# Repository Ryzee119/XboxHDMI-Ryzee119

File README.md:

# Original Xbox 100% Digital HDMI (Prototype)

**Note: This is a 'working' but unfinished prototype. I don't plan to improve this further. See https://makemhz.com/products/xboxhd for a properly finished product with way more features.**

* A few HDMI captures taken from this board are here: https://imgur.com/a/OkmB1Vs
* This is a prototype 100% digital Original Xbox HDMI addon PCB. It taps into the GPU pixel bus before it enters the analog video encoder and converts it to a HDMI compliant signal.
* It has not been fully tested and may not work for you. Use at your own risk. This should only really be a starting point to make something better.
* SPDIF digital audio is tapped off the Xbox motherboard and is also encoded into the HDMI signal for the best possible audio quality.
* This is a prototype board which should work on all Xbox revisions however a new flex would need to be designed to accomodate v1.6 motherboards with an Xcalibur encoder.
* 480i does not work reliably. Use a force 480p BIOS.
* The xbox kernels video modes are not compliant to proper HDMI signalling (v/hsync, porch delays etc). This does not have the ability to correct that. If your display is picky it may just not display anything.
* Currently the MakeMHz solution is recommended. https://makemhz.com/products/xboxhd. It is a completely independent design which has been much more tested and with more features.

## Bill of materials
* See [Kitspace](https://kitspace.org/boards/github.com/ryzee119/XboxHDMI-Ryzee119/).
* Flatflex must be ordered separately. See [hardware](./hardware).

## Design Files
* Source code for the STM32F0 driver is [here](./src).
* Hardware design files are [here](./hardware).

## Programming
* Compile the code with [VSCode](https://code.visualstudio.com/) and the [platformIO](https://platformio.org/install/ide?install=vscode) plugin. It should automatically create the build sytem. Just click build.
* The STM32F07 driver must be programmed with the firmware.
* Programming is through the 5 pin SWD header on the PCB. Pinout from left to right: `+3V3, SWDCLK, GND, SWDIO, NRST`
* Some debug output is via the pad labelled `TX`. Baud 115200.

## Installation

* Photo may not match final PCB layout.

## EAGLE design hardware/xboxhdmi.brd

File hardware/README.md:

# Hardware

* This board was designed using [Autodesk Eagle](https://www.autodesk.com/products/eagle/overview). You can edit the `.brd` and `.sch` with this program.

## View Gerbers
* [XboxHDMI PCB](https://tracespace.io/view/?boardUrl=https://github.com/Ryzee119/XboxHDMI-Ryzee119/blob/master/hardware/gerbers_xboxhdmi.zip?raw=true)
* [FlatFlex PCB](https://tracespace.io/view/?boardUrl=https://github.com/Ryzee119/XboxHDMI-Ryzee119/blob/master/hardware/gerbers_conex_focus_flex.zip?raw=true)

## View Board and Schematic
* [Board](https://a360.co/3of4zFJ)
* [Schematic](https://a360.co/2LYpuQg)

## 3D Render
* [Fusion 360](https://a360.co/2KIBkxm)

### Flat Flex Properties
* 2 Layers
* Polyimide Flex
* FPC Thickness: 0.10 mm
* Stiffener: BOTTOM Plastic : 0.20 mm , BOTTOM Fr4 : 0 mm , BOTTOM Metal : 0 mm
* Total thickness at stiffener should be 0.30 mm.
* Stiffener location: See image

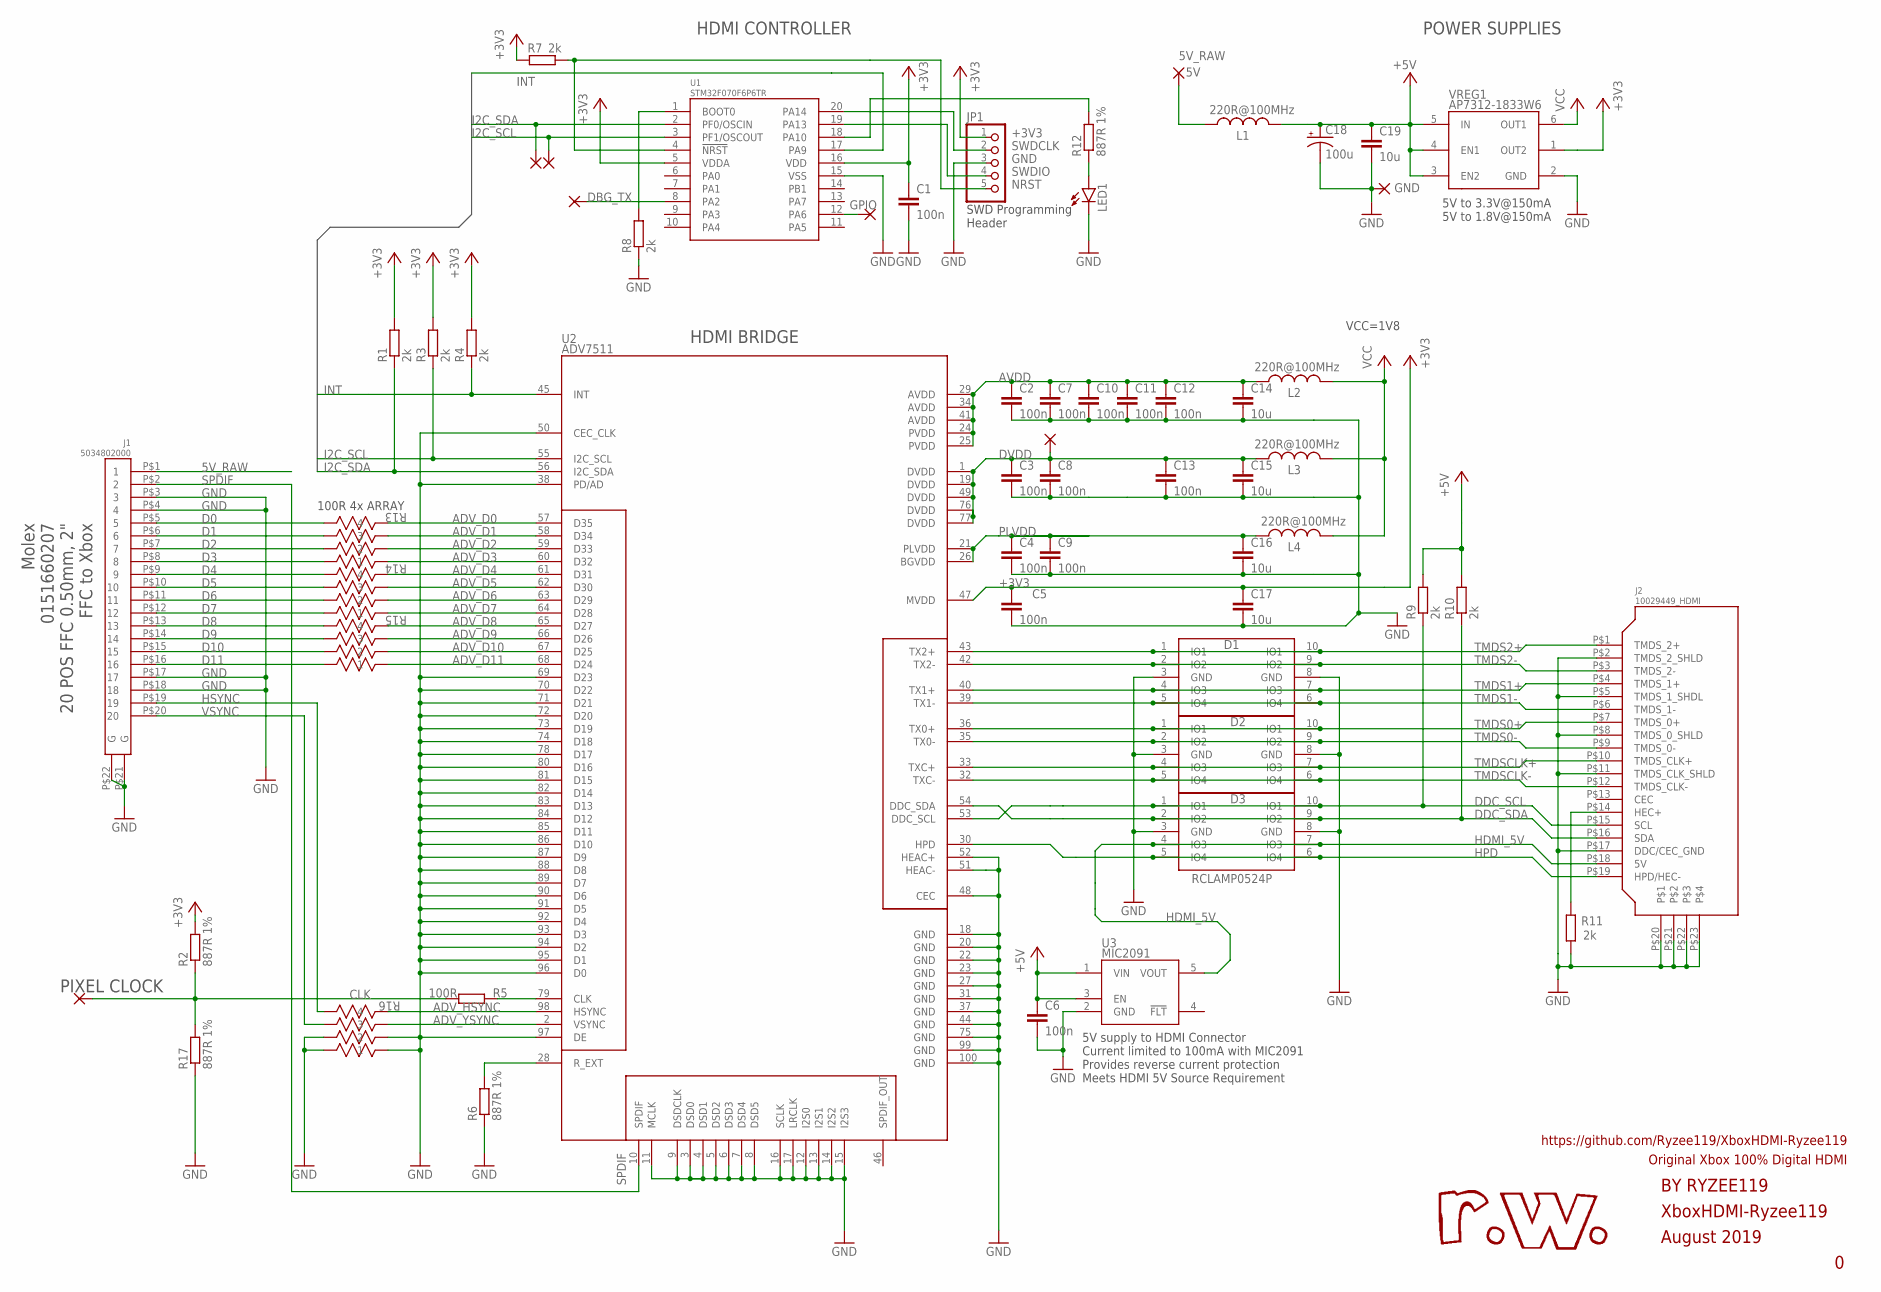
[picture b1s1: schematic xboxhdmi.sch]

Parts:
1V8, 5V: SMD2; SMD1,27-2,54
C1, C2, C3, C4, C5, C6, C7, C8, C9, C10, C11, C12, C13: 100n; C0603
C14, C15, C16, C17, C19: 10u; C1206
C18: 100u; 153CLV-0505
CLK: SMD2; SMD1,27-2,54
D1, D2, D3: RCLAMP0524P; DIOCAF50P250X100X65-10
GND: SMD2; SMD1,27-2,54
J1: 5034802000
J2: 10029449_HDMI; HDMI_10029449
JP1: PINHD-1X5; 1X05
L1, L2, L3, L4: 220R@100MHz; C0603
LED1: LEDCHIP-LED0603; CHIP-LED0603
PAD3, PAD4, PAD5: SMD2; SMD1,27-2,54
R1, R3, R4, R7, R8, R9, R10, R11: 2k; R0603
R2, R6, R12, R17: 887R 1%; R0603
R5: 100R; R0603
R13, R14, R15, R16: YC124-JR-0733RL; YAG_YC124
TX: SMD2; SMD1,27-2,54
U1: STM32F070F6P6TR; TSSOP20
U2: ADV7511; LQFP100
U3: MIC2091; SOT23-5
VREG1: AP7312-1833W6; SOT23-6

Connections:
5V_RAW: 5V.1, J1.P$1 (1), L1.1
+3V3: C1.1, C5.1, C17.1, JP1.1, R1.2, R2.2, R3.2, R4.2, R7.2, U1.5 (VDDA), U1.16 (VDD), U2.47 (MVDD), VREG1.1 (OUT2)
+5V: C6.1, C18.+, C19.1, L1.2, R9.2, R10.2, U3.1 (VIN), U3.3 (EN), VREG1.3 (EN2), VREG1.4 (EN1), VREG1.5 (IN)
ADV_CLK: R5.1, U2.79 (CLK)
ADV_D0: R13.4, U2.57 (D35)
ADV_D1: R13.3, U2.58 (D34)
ADV_D2: R13.2, U2.59 (D33)
ADV_D3: R13.1, U2.60 (D32)
ADV_D4: R14.4, U2.61 (D31)
ADV_D5: R14.3, U2.62 (D30)
ADV_D6: R14.2, U2.63 (D29)
ADV_D7: R14.1, U2.64 (D28)
ADV_D8: R15.4, U2.65 (D27)
ADV_D9: R15.3, U2.66 (D26)
ADV_D10: R15.2, U2.67 (D25)
ADV_D11: R15.1, U2.68 (D24)
ADV_HSYNC: R16.4, U2.98 (HSYNC)
ADV_YSYNC: R16.3, U2.2 (VSYNC)
AVDD: C2.1, C7.1, C10.1, C11.1, C12.1, C14.1, L2.1, U2.24 (PVDD), U2.25 (PVDD), U2.29 (AVDD), U2.34 (AVDD), U2.41 (AVDD)
CLK: CLK.1, R2.1, R5.2, R17.2
D0: J1.P$5 (5), R13.5
D1: J1.P$6 (6), R13.6
D2: J1.P$7 (7), R13.7
D3: J1.P$8 (8), R13.8
D4: J1.P$9 (9), R14.5
D5: J1.P$10 (10), R14.6
D6: J1.P$11 (11), R14.7
D7: J1.P$12 (12), R14.8
D8: J1.P$13 (13), R15.5
D9: J1.P$14 (14), R15.6
D10: J1.P$15 (15), R15.7
D11: J1.P$16 (16), R15.8
DBG_TX: TX.1, U1.8 (PA2)
DDC_SCL: D3.1 (IO1), D3.10 (IO1), J2.P$15 (SCL), R9.1, U2.53 (DDC_SCL)
DDC_SDA: D3.2 (IO2), D3.9 (IO2), J2.P$16 (SDA), R10.1, U2.54 (DDC_SDA)
DVDD: 1V8.1, C3.1, C8.1, C13.1, C15.1, L3.1, U2.1 (DVDD), U2.19 (DVDD), U2.49 (DVDD), U2.76 (DVDD), U2.77 (DVDD)
GND: C1.2, C2.2, C3.2, C4.2, C5.2, C6.2, C7.2, C8.2, C9.2, C10.2, C11.2, C12.2, C13.2, C14.2, C15.2, C16.2, C17.2, C18.-, C19.2, D1.3 (GND), D1.8 (GND), D2.3 (GND), D2.8 (GND), D3.3 (GND), D3.8 (GND), GND.1, J1.P$3 (3), J1.P$4 (4), J1.P$17 (17), J1.P$18 (18), J1.P$21 (G), J1.P$22 (G), J2.P$2 (TMDS_2_SHLD), J2.P$5 (TMDS_1_SHDL), J2.P$8 (TMDS_0_SHLD), J2.P$11 (TMDS_CLK_SHLD), J2.P$17 (DDC/CEC_GND), J2.P$20, J2.P$21, J2.P$22, J2.P$23, JP1.3, LED1.C, R6.1, R8.1, R11.1, R16.1, R16.2, R16.7, R16.8, R17.1, U1.15 (VSS), U2.3 (DSD0), U2.4 (DSD1), U2.5 (DSD2), U2.6 (DSD3), U2.7 (DSD4), U2.8 (DSD5), U2.9 (DSDCLK), U2.11 (MCLK), U2.12 (I2S0), U2.13 (I2S1), U2.14 (I2S2), U2.15 (I2S3), U2.16 (SCLK), U2.17 (LRCLK), U2.18 (GND), U2.20 (GND), U2.22 (GND), U2.23 (GND), U2.27 (GND), U2.31 (GND), U2.37 (GND), U2.38 (PD/AD), U2.44 (GND), U2.48 (CEC), U2.50 (CEC_CLK), U2.51 (HEAC-), U2.52 (HEAC+), U2.69 (D23), U2.70 (D22), U2.71 (D21), U2.72 (D20), U2.73 (D19), U2.74 (D18), U2.75 (GND), U2.78 (D17), U2.80 (D16), U2.81 (D15), U2.82 (D14), U2.83 (D13), U2.84 (D12), U2.85 (D11), U2.86 (D10), U2.87 (D9), U2.88 (D8), U2.89 (D7), U2.90 (D6), U2.91 (D5), U2.92 (D4), U2.93 (D3), U2.94 (D2), U2.95 (D1), U2.96 (D0), U2.97 (DE), U2.99 (GND), U2.100 (GND), U3.2 (GND), VREG1.2 (GND)
GPIO: PAD5.1, U1.12 (PA6)
HDMI_5V: D3.4 (IO3), D3.7 (IO3), J2.P$18 (5V), U3.5 (VOUT)
HEC+: J2.P$14 (HEC+), R11.2
HPD: D3.5 (IO4), D3.6 (IO4), J2.P$19 (HPD/HEC-), U2.30 (HPD)
HSYNC: J1.P$19 (19), R16.5
I2C_SCL: PAD4.1, R3.1, U1.3 (PF1/OSCOUT), U2.55 (I2C_SCL)
I2C_SDA: PAD3.1, R1.1, U1.2 (PF0/OSCIN), U2.56 (I2C_SDA)
INT: R4.1, U1.17 (PA9), U2.45 (INT)
unnamed: R12.2, U1.18 (PA10)
unnamed: LED1.A, R12.1
unnamed: R8.2, U1.1 (BOOT0)
NRST: JP1.5, R7.1, U1.4 (!NRST)
PLVDD: C4.1, C9.1, C16.1, L4.1, U2.21 (PLVDD), U2.26 (BGVDD)
R_EXT: R6.2, U2.28 (R_EXT)
SPDIF: J1.P$2 (2), U2.10 (SPDIF)
SWDCLK: JP1.2, U1.20 (PA14)
SWDIO: JP1.4, U1.19 (PA13)
TMDS0+: D2.1 (IO1), D2.10 (IO1), J2.P$7 (TMDS_0+), U2.36 (TX0+)
TMDS0-: D2.2 (IO2), D2.9 (IO2), J2.P$9 (TMDS_0-), U2.35 (TX0-)
TMDS1+: D1.4 (IO3), D1.7 (IO3), J2.P$4 (TMDS_1+), U2.40 (TX1+)
TMDS1-: D1.5 (IO4), D1.6 (IO4), J2.P$6 (TMDS_1-), U2.39 (TX1-)
TMDS2+: D1.1 (IO1), D1.10 (IO1), J2.P$1 (TMDS_2+), U2.43 (TX2+)
TMDS2-: D1.2 (IO2), D1.9 (IO2), J2.P$3 (TMDS_2-), U2.42 (TX2-)
TMDSCLK+: D2.4 (IO3), D2.7 (IO3), J2.P$10 (TMDS_CLK+), U2.33 (TXC+)
TMDSCLK-: D2.5 (IO4), D2.6 (IO4), J2.P$12 (TMDS_CLK-), U2.32 (TXC-)
VCC: L2.2, L3.2, L4.2, VREG1.6 (OUT1)
VSYNC: J1.P$20 (20), R16.6

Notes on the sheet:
VCC=1V8
5V supply to HDMI Connector Current limited to 100mA with MIC2091 Provides reverse current protection Meets HDMI 5V Source Requirement
XboxHDMI-Ryzee119
August 2019
BY RYZEE119
Original Xbox 100% Digital HDMI
https://github.com/Ryzee119/XboxHDMI-Ryzee119
SWD Programming Header
5V to 3.3V@150mA 5V to 1.8V@150mA
POWER SUPPLIES
HDMI CONTROLLER
HDMI BRIDGE
Molex 0151660207 20 POS FFC 0.50mm, 2" FFC to Xbox
PIXEL CLOCK
100R 4x ARRAY

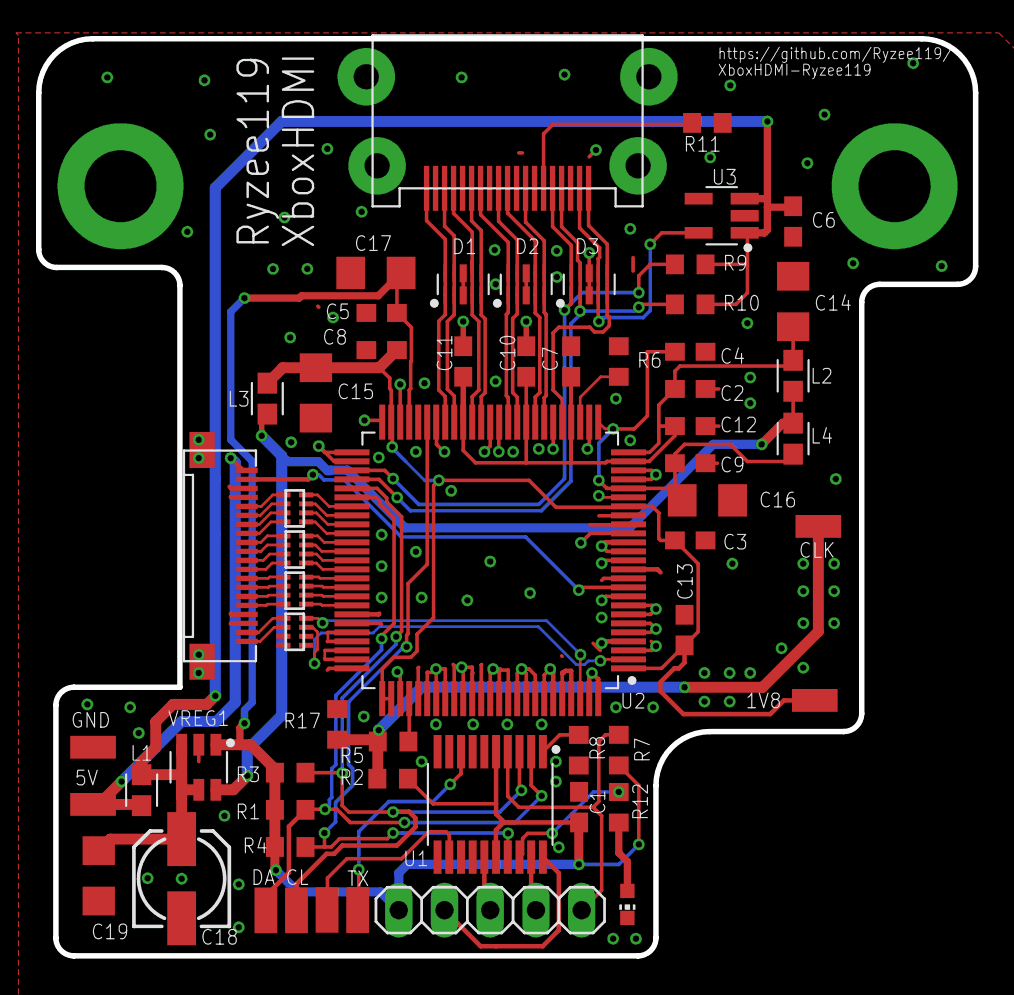
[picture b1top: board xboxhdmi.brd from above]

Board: 2 copper layers, 52.0 x 51.0 mm, 59 parts (0 on the bottom side), 64 nets.

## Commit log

2021-01-25 HW: Add Render Link
2021-01-25 HW: Add board and schematic viewer links
2021-02-13 SW: Allow compilation for stm32f04
2021-02-13 SW: Remove clock hacks
2021-02-13 HW: Remove old notes
2021-02-13 HW: Board cleanup
2021-02-13 Main: Upload images
2021-02-13 Kitspace: Add initial support
2021-02-13 README: Create readme
2021-07-16 Github: Add License
2021-07-16 Readme: Add extra note
2021-07-16 Readme: Add programming details
2022-03-09 Readme: Disclaimers..
2022-03-09 README: Typo
2022-03-09 Kitspace: Add `eda` field
2022-03-10 Typo fix in README.md
